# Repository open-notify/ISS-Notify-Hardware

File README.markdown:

# ISS Notify Hardware

ISS Notify is an open hardware project to make a desktop notification lamp
specifically for overhead passes for the International Space Station for a
users location.

ISS Notify is a simple 2 layer board with an AVR microcontroller with USB
and a set of RGB LEDs LED driver/shift registers. It also has a 
real time clock and a LiPo batter charging circuit.

This repo has all of the design files needed for producing the hardware.

Designed in Eagle version 6.3.

Licensed under the TAPR Open Hardware License (www.tapr.org/OHL). See 
LICENSE.txt for full license information.

 - Download pdf [schematic.pdf](https://github.com/open-notify/ISS-Notify-Hardware/raw/master/schematic.pdf)

 - Download pdf [board.pdf](https://github.com/open-notify/ISS-Notify-Hardware/raw/master/board.pdf)

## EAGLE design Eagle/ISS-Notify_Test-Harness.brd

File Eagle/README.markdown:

# Eagle Files

 - `eagle.epf`: Eagle project
 - `ISS-Notify.lbr`: Eagle parts library
 - `ISS-Notify.sch`: Main board schematic
 - `ISS-Notify.brd`: Main board boardfile
 - `ISS-Notify_Test-Harness.sch`: Test Harness schematic
 - `ISS-Notify_Test-Harness.brd`: Test Harness board

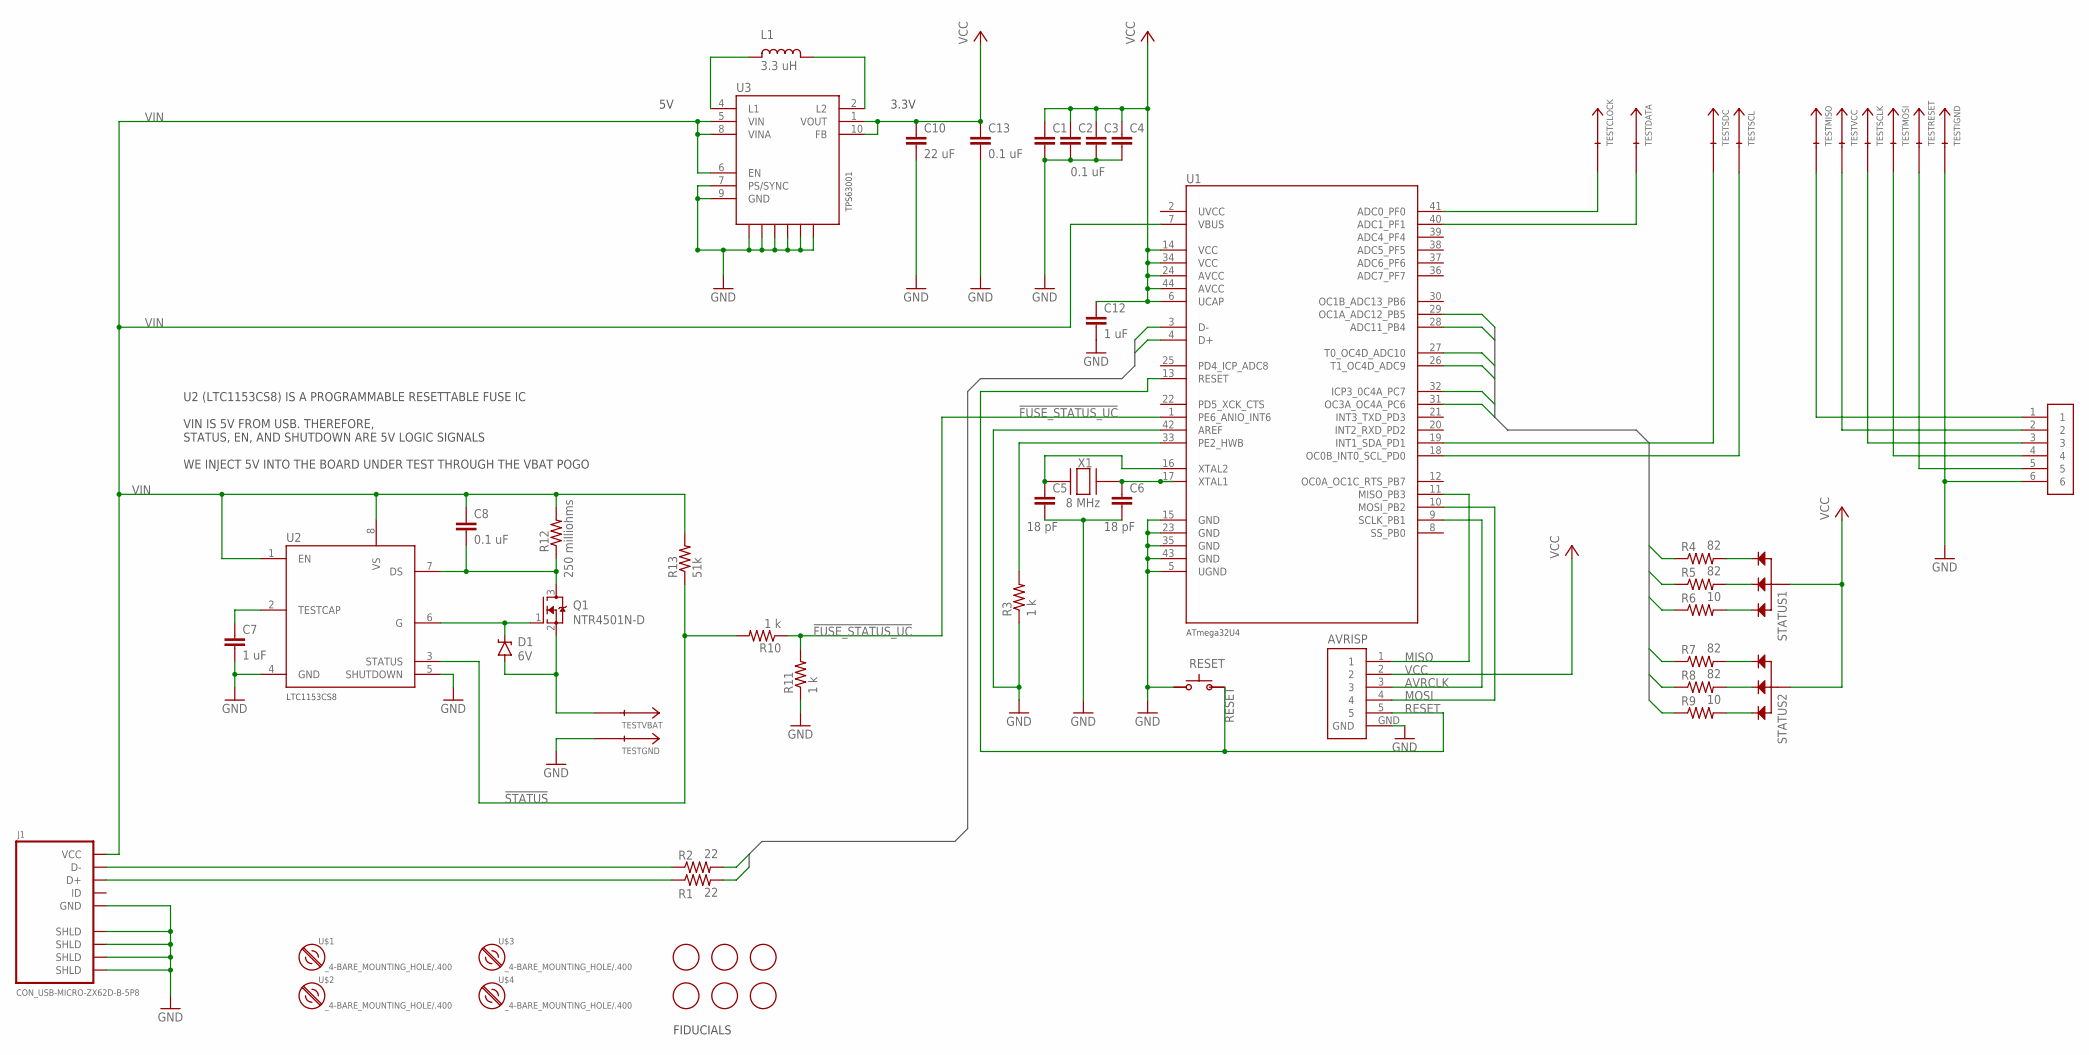
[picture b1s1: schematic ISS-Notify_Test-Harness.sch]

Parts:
AVRISP: AVRISP
C1, C2, C3, C4, C8, C13: 0.1 uF; 0603-C-NOSILK
C5, C6: 18 pF; 0603-C-NOSILK
C7, C12: 1 uF; 0603-C-NOSILK
C10: 22 uF; 0805-C-NOSILK
D1: 6V; SOD-323
F1, F2, F3, F4, F5, F6: FIDUCIAL; FIDUCIAL_1MM
J1: CON_USB-MICRO-ZX62D-B-5P8; USBMICROSMT-HIROSE
JPROGRAMER: 6HEADER; 6HEAD
L1: 3.3 uH; 0805-C-NOSILK
Q1: NTR4501N-D; SOT-23
R1, R2: 22; 0603-C-NOSILK
R3, R10, R11: 1 k; 0603-C-NOSILK
R4, R5, R7, R8: 82; 0603-C-NOSILK
R6, R9: 10; 0603-C-NOSILK
R12: 250 milliohms; 0603-C-NOSILK
R13: 51k; 0603-C-NOSILK
RESET: SWITCH
STATUS1, STATUS2: RGBLED; SMDRGBLED
TESTCLOCK: POGOPIN
TESTDATA: POGOPIN
TESTGND: POGOPIN
TESTIGND: POGOPIN
TESTMISO: POGOPIN
TESTMOSI: POGOPIN
TESTRESET: POGOPIN
TESTSCL: POGOPIN
TESTSCLK: POGOPIN
TESTSDC: POGOPIN
TESTVBAT: POGOPIN
TESTVCC: POGOPIN
U1: ATMEGA32U4; TQFP-44
U2: LTC1153CS8; SO-8
U3: TPS63001; QFN10
U$1, U$2, U$3, U$4: _4-BARE_MOUNTING_HOLE/.400; _4/.400-BARE+STD_TOOL_CLEARANCE
X1: 8 MHz; CX5Z

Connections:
!FUSE_STATUS_UC: R10.1, R11.2, U1.1 (PE6_ANIO_INT6)
!STATUS: R10.2, R13.1, U2.3 (STATUS)
AVRCLK: AVRISP.3, U1.9 (SCLK_PB1)
D+: R1.2, U1.4 (D+)
D-: R2.2, U1.3 (D-)
GND: AVRISP.GND, C1.2, C2.2, C3.2, C4.2, C5.2, C6.2, C7.2, C10.2, C12.2, C13.2, J1.P5 (GND), J1.P$1 (SHLD), J1.P$2 (SHLD), J1.P$3 (SHLD), J1.P$4 (SHLD), JPROGRAMER.6, R3.1, R11.1, RESET.3 (2), TESTGND.1, TESTIGND.1, U1.5 (UGND), U1.15 (GND), U1.23 (GND), U1.35 (GND), U1.42 (AREF), U1.43 (GND), U2.4 (GND), U2.5 (SHUTDOWN), U3.3 (PGND), U3.7 (PS/SYNC), U3.9 (GND), U3.PAD (GNDPAD), U3.PGND1, U3.PGND2, U3.PGND3, U3.PGND4
LED1_B: R6.1, U1.29 (OC1A_ADC12_PB5)
LED1_G: R5.1, U1.32 (ICP3_0C4A_PC7)
LED1_R: R4.1, U1.31 (OC3A_OC4A_PC6)
LED2_B: R9.1, U1.26 (T1_OC4D_ADC9)
LED2_G: R8.1, U1.28 (ADC11_PB4)
LED2_R: R7.1, U1.27 (T0_OC4D_ADC10)
LED_CLK: TESTCLOCK.1, U1.41 (ADC0_PF0)
LED_DATA: TESTDATA.1, U1.40 (ADC1_PF1)
MISO: AVRISP.1, U1.11 (MISO_PB3)
MOSI: AVRISP.4, U1.10 (MOSI_PB2)
unnamed: L1.1 (A), U3.4 (L1)
unnamed: L1.2 (C), U3.2 (L2)
unnamed: R4.2, STATUS1.RED (R)
unnamed: J1.P3 (D+), R1.1
unnamed: J1.P2 (D-), R2.1
unnamed: C5.1, U1.16 (XTAL2), X1.1
unnamed: R5.2, STATUS1.GREEN (G)
unnamed: R6.2, STATUS1.BLUE (B)
unnamed: R7.2, STATUS2.RED (R)
unnamed: C6.1, U1.17 (XTAL1), X1.3 (2)
unnamed: R8.2, STATUS2.GREEN (G)
unnamed: R9.2, STATUS2.BLUE (B)
unnamed: C7.1, U2.2 (TESTCAP)
unnamed: C8.2, Q1.3 (D), R12.1, U2.7 (DS)
unnamed: D1.C, Q1.1 (G), U2.6 (G)
unnamed: D1.A, Q1.2 (S), TESTVBAT.1
unnamed: R3.2, U1.33 (PE2_HWB)
RESET: AVRISP.5, RESET.1, U1.13 (RESET)
SCL: TESTSCL.1, U1.18 (OC0B_INT0_SCL_PD0)
SDA: TESTSDC.1, U1.19 (INT1_SDA_PD1)
TESTMISO: JPROGRAMER.1, TESTMISO.1
TESTMOSI: JPROGRAMER.4, TESTMOSI.1
TESTRESET: JPROGRAMER.5, TESTRESET.1
TESTSCLK: JPROGRAMER.3, TESTSCLK.1
TESTVCC: JPROGRAMER.2, TESTVCC.1
UVCC: U1.2 (UVCC)
VCC: AVRISP.2, C1.1, C2.1, C3.1, C4.1, C10.1, C12.1, C13.1, STATUS1.ANODE, STATUS2.ANODE, U1.6 (UCAP), U1.14 (VCC), U1.24 (AVCC), U1.34 (VCC), U1.44 (AVCC), U3.1 (VOUT), U3.10 (FB)
VIN: C8.1, J1.P1 (VCC), R12.2, R13.2, U1.7 (VBUS), U2.1 (EN), U2.8 (VS), U3.5 (VIN), U3.6 (EN), U3.8 (VINA)

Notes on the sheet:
3.3V
U2 (LTC1153CS8) IS A PROGRAMMABLE RESETTABLE FUSE IC VIN IS 5V FROM USB. THEREFORE, STATUS, EN, AND SHUTDOWN ARE 5V LOGIC SIGNALS WE INJECT 5V INTO THE BOARD UNDER TEST THROUGH THE VBAT POGO
FIDUCIALS

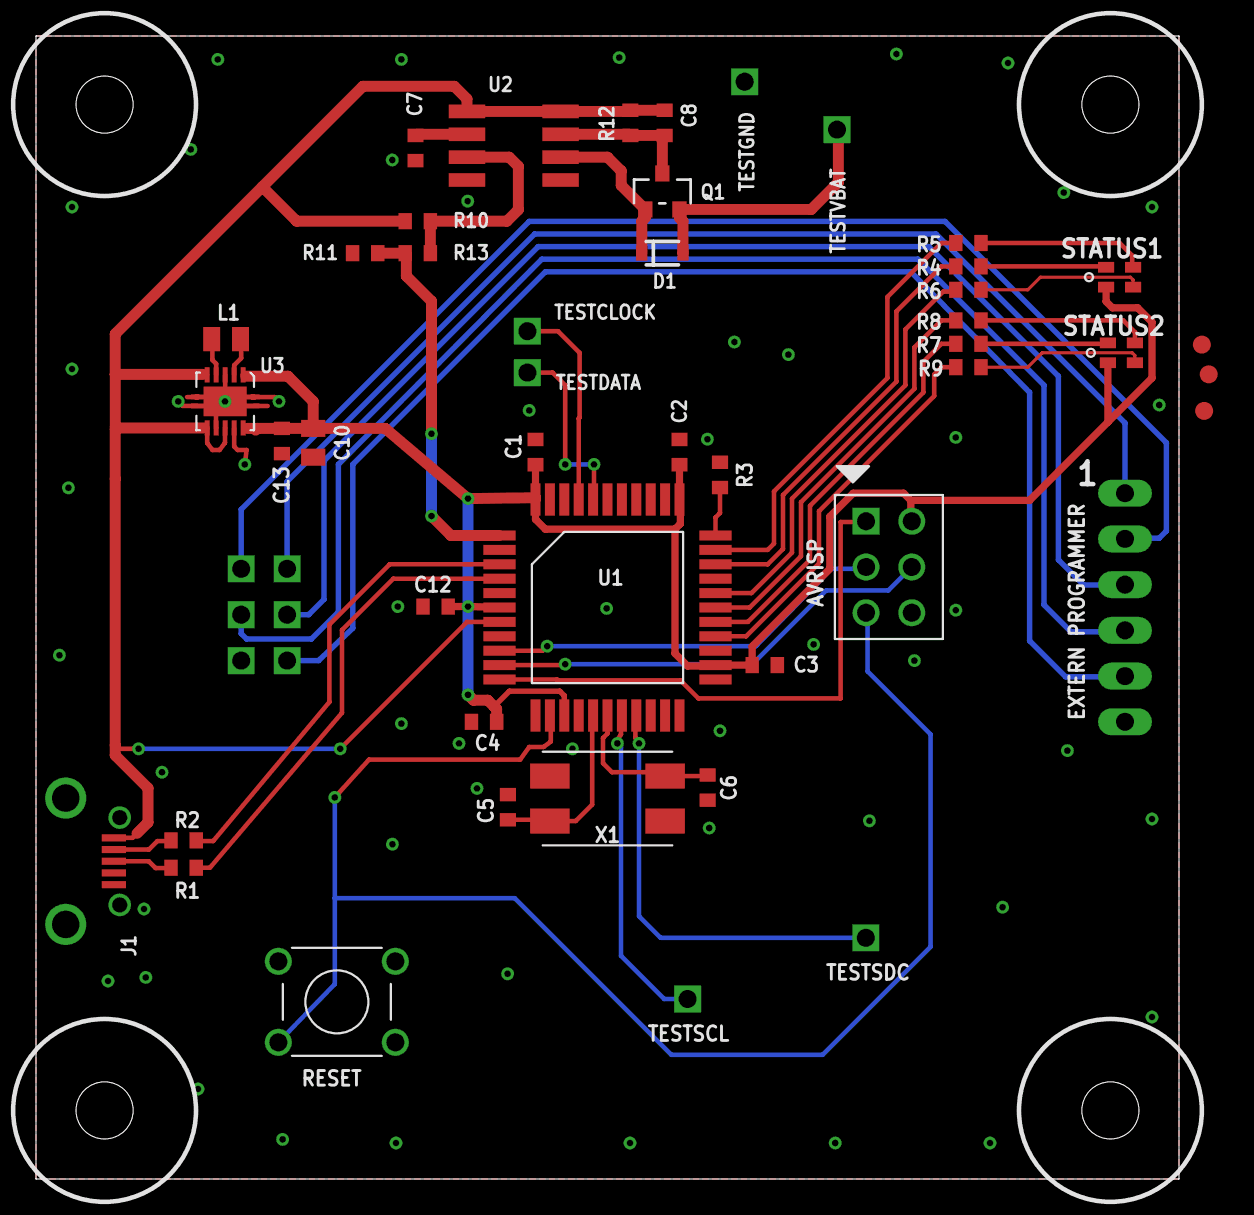
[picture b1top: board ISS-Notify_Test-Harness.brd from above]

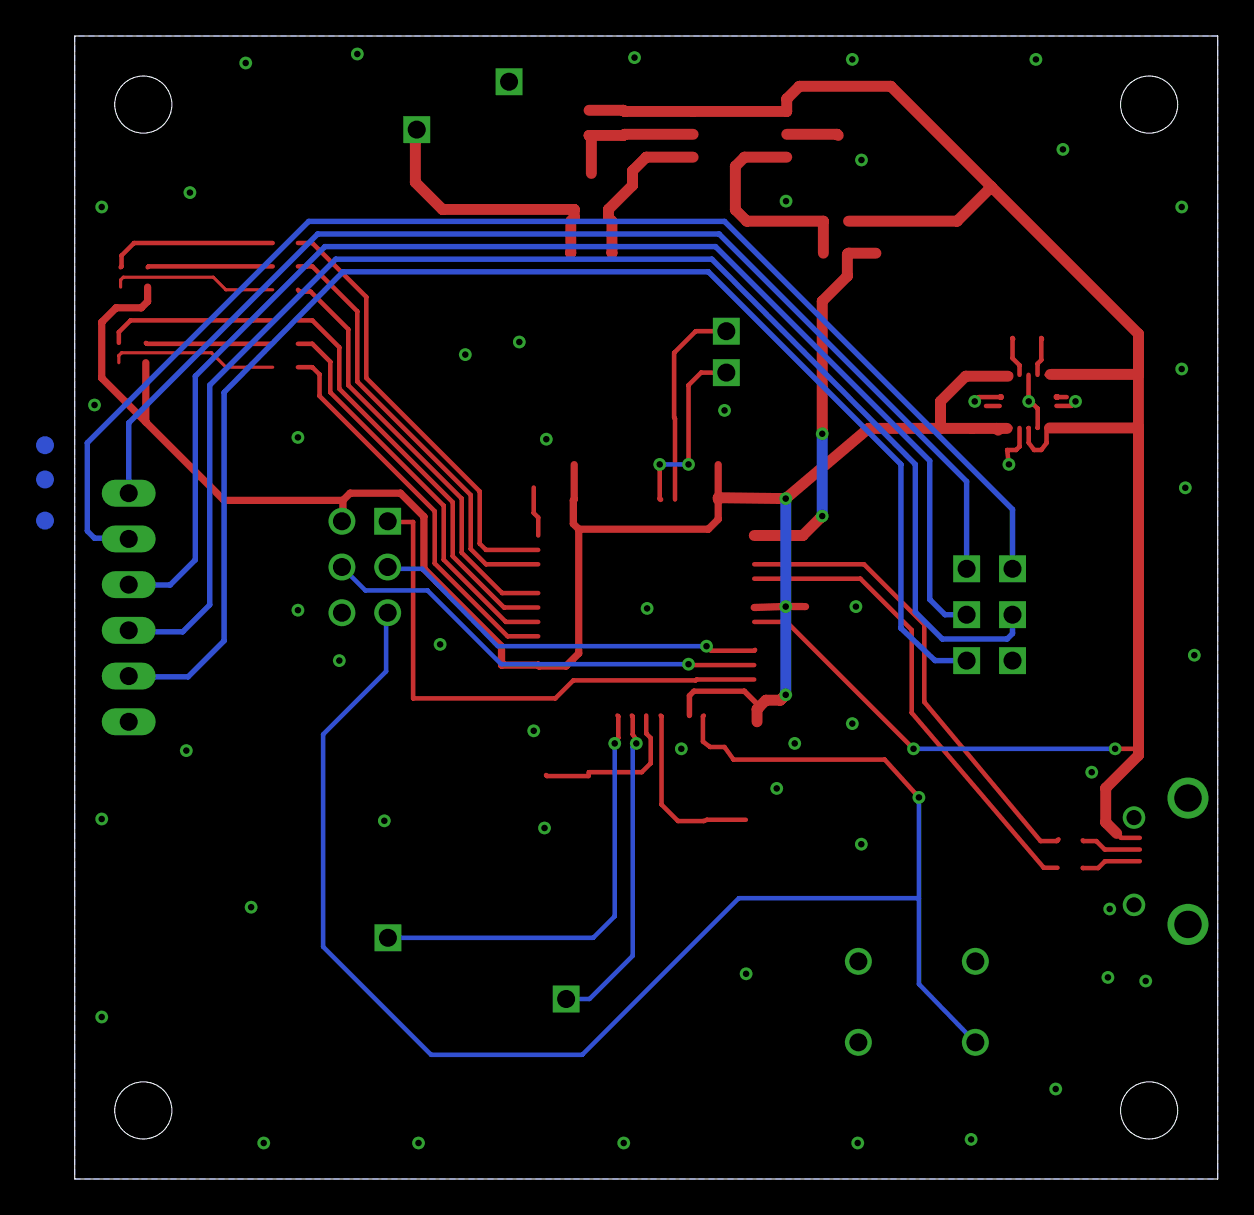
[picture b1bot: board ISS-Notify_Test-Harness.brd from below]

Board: 2 copper layers, 63.5 x 63.5 mm, 59 parts (3 on the bottom side), 43 nets.

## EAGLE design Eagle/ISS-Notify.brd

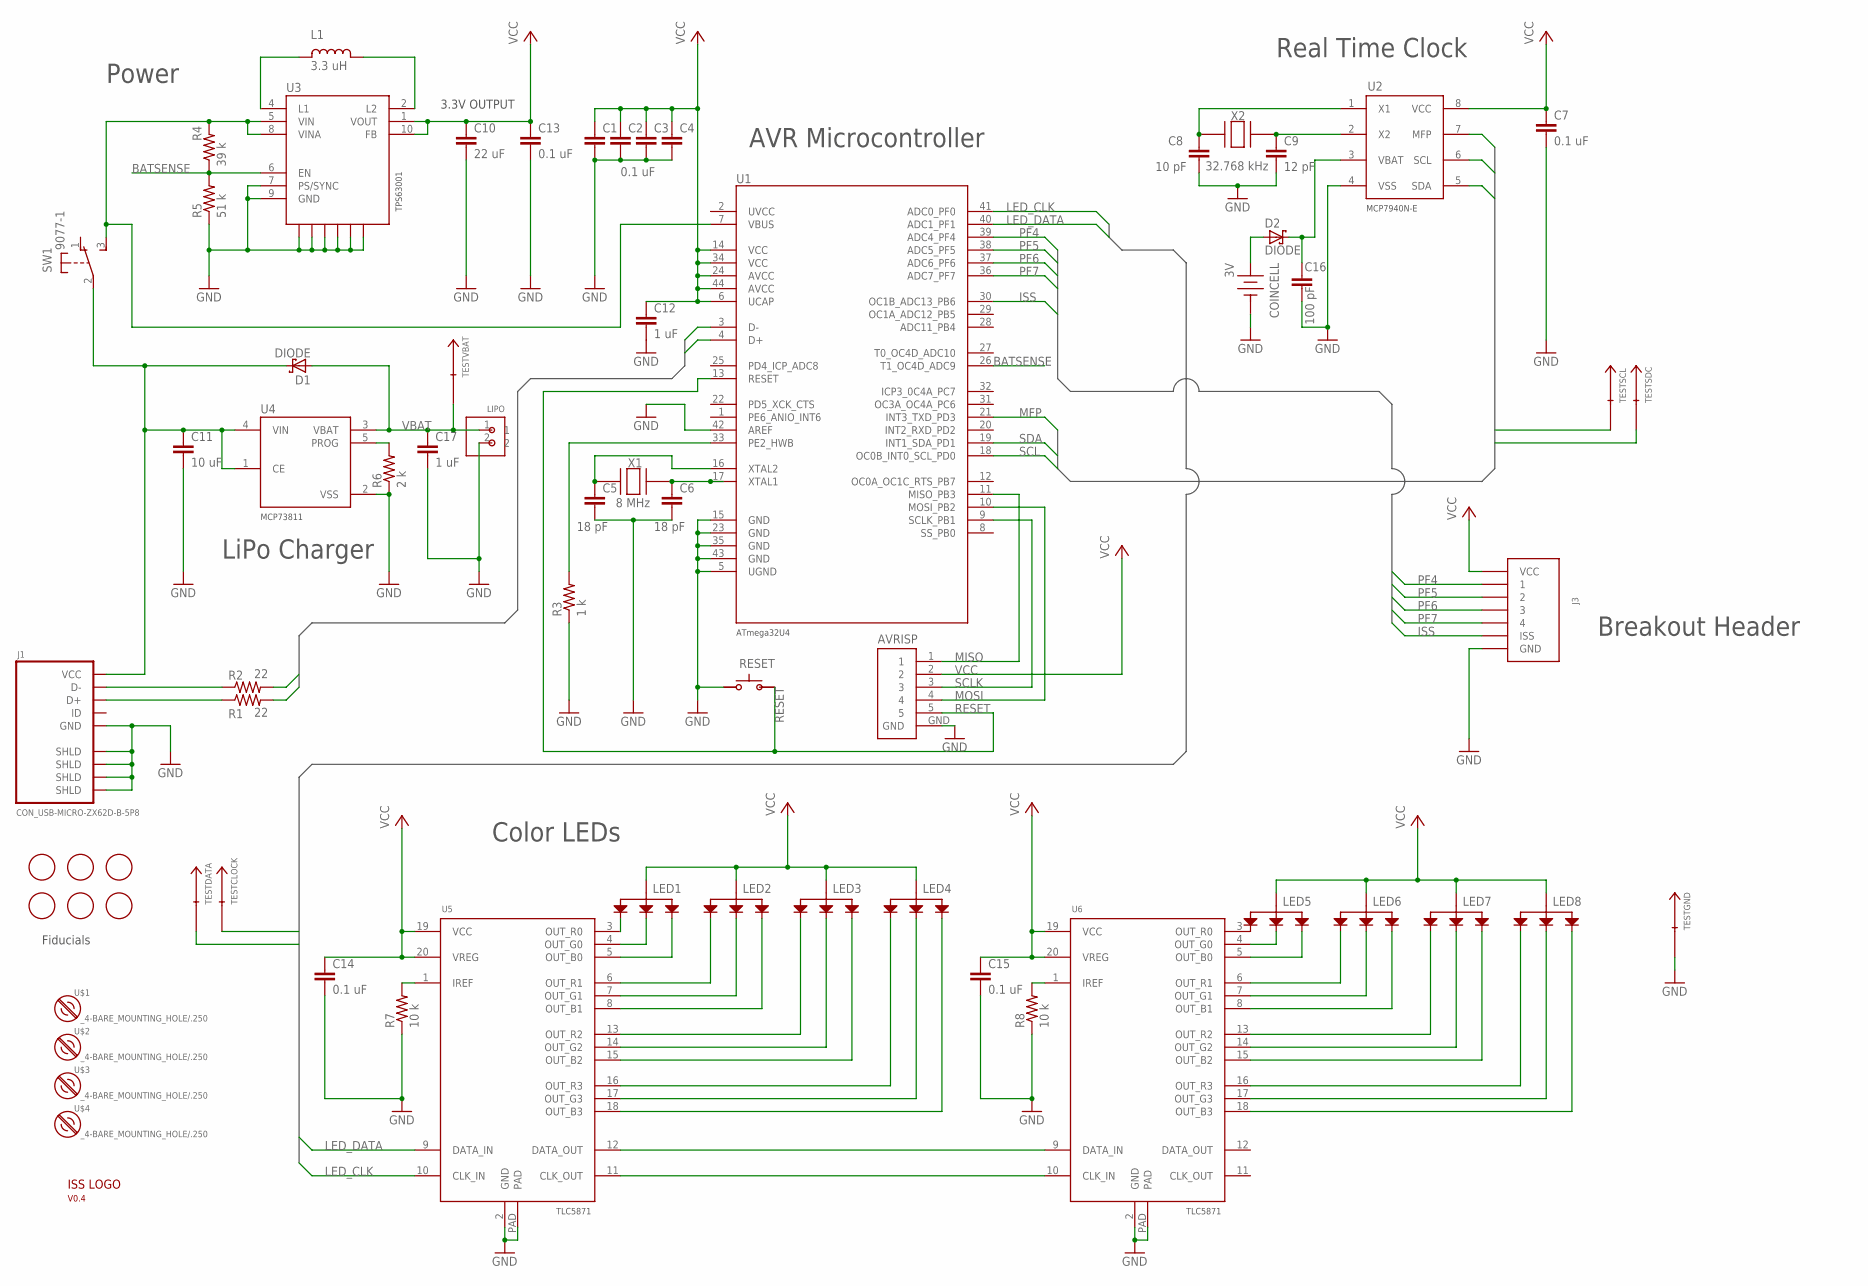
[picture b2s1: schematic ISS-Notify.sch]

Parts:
AVRISP: AVRISP
C1, C2, C3, C4, C7, C13, C14, C15: 0.1 uF; 0603-C-NOSILK
C5, C6: 18 pF; 0603-C-NOSILK
C8: 10 pF; 0603-C-NOSILK
C9: 12 pF; 0603-C-NOSILK
C10: 22 uF; 0805-C-NOSILK
C11: 10 uF; 0805-C-NOSILK
C12, C17: 1 uF; 0603-C-NOSILK
C16: 100 pF; 0603-C-NOSILK
COINCELL: 3V; COINCELL
D1, D2: DIODE; 0805-DIODE
J1: CON_USB-MICRO-ZX62D-B-5P8; USBMICROSMT-HIROSE
J3: PROTOSPACE2
L1: 3.3 uH; 0805-C-NOSILK
LED1, LED2, LED3, LED4, LED5, LED6, LED7, LED8: RGBLED; SMDRGBLED
LIPO: JST2; JSTHEAD
R1, R2: 22; 0603-C-NOSILK
R3: 1 k; 0603-C-NOSILK
R4: 39 k; 0603-C-NOSILK
R5: 51 k; 0603-C-NOSILK
R6: 2 k; 0603-C-NOSILK
R7, R8: 10 k; 0603-C-NOSILK
RESET: SWITCH
SW1: 9077-1; ESWITCH
TESTCLOCK: TESTPIN
TESTDATA: TESTPIN
TESTGND: TESTPIN
TESTSCL: TESTPIN
TESTSDC: TESTPIN
TESTVBAT: TESTPIN
U1: ATMEGA32U4; TQFP-44
U2: MCP7940N
U3: TPS63001; QFN10
U4: MCP73811; SOT23-5L
U5, U6: TLC5971; R-PDSO-G20
U$1, U$2, U$3, U$4: _4-BARE_MOUNTING_HOLE/.250; _4/.250-BARE+STD_WASHER
U$5: V0.4; LOGO
U$6, U$7, U$8, U$9, U$10, U$11: FIDUCIAL; FIDUCIAL_1MM
X1: 8 MHz; CX5Z
X2: 32.768 kHz; ABS10

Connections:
BATSENSE: R4.1, R5.2, U1.26 (T1_OC4D_ADC9), U3.6 (EN)
D+: R1.2, U1.4 (D+)
D-: R2.2, U1.3 (D-)
GND: AVRISP.GND, C1.2, C2.2, C3.2, C4.2, C5.2, C6.2, C7.2, C8.2, C9.2, C10.2, C11.2, C12.2, C13.2, C14.2, C15.2, C16.2, C17.2, COINCELL.GND, J1.P5 (GND), J1.P$1 (SHLD), J1.P$2 (SHLD), J1.P$3 (SHLD), J1.P$4 (SHLD), J3.GND, LIPO.2, R3.1, R5.1, R6.1, R7.1, R8.1, RESET.3 (2), TESTGND.P$1, U1.5 (UGND), U1.15 (GND), U1.23 (GND), U1.35 (GND), U1.42 (AREF), U1.43 (GND), U2.4 (VSS), U3.3 (PGND), U3.7 (PS/SYNC), U3.9 (GND), U3.PAD (GNDPAD), U3.PGND1, U3.PGND2, U3.PGND3, U3.PGND4, U4.2 (VSS), U5.2 (GND), U5.PAD, U6.2 (GND), U6.PAD
ISS: J3.ISS, U1.30 (OC1B_ADC13_PB6)
LED_CLK: TESTCLOCK.P$1, U1.41 (ADC0_PF0), U5.10 (CLK_IN)
LED_DATA: TESTDATA.P$1, U1.40 (ADC1_PF1), U5.9 (DATA_IN)
MFP: U1.21 (INT3_TXD_PD3), U2.7 (MFP)
MISO: AVRISP.1, U1.11 (MISO_PB3)
MOSI: AVRISP.4, U1.10 (MOSI_PB2)
unnamed: L1.1 (A), U3.4 (L1)
unnamed: L1.2 (C), U3.2 (L2)
unnamed: J1.P3 (D+), R1.1
unnamed: J1.P2 (D-), R2.1
unnamed: C5.1, U1.16 (XTAL2), X1.1
unnamed: C9.1, U2.2 (X2), X2.@1 (2)
unnamed: C8.1, U2.1 (X1), X2.1
unnamed: C6.1, U1.17 (XTAL1), X1.3 (2)
unnamed: COINCELL.POS1 (VBAT), D2.A
unnamed: R6.2, U4.5 (PROG)
unnamed: U5.11 (CLK_OUT), U6.10 (CLK_IN)
unnamed: U5.12 (DATA_OUT), U6.9 (DATA_IN)
unnamed: C16.1, D2.C, U2.3 (VBAT)
unnamed: LED2.BLUE (B), U5.8 (OUT_B1)
unnamed: R7.2, U5.1 (IREF)
unnamed: R8.2, U6.1 (IREF)
unnamed: LED3.RED (R), U5.13 (OUT_R2)
unnamed: LED3.GREEN (G), U5.14 (OUT_G2)
unnamed: LED3.BLUE (B), U5.15 (OUT_B2)
unnamed: LED1.RED (R), U5.3 (OUT_R0)
unnamed: LED1.GREEN (G), U5.4 (OUT_G0)
unnamed: LED1.BLUE (B), U5.5 (OUT_B0)
unnamed: LED2.RED (R), U5.6 (OUT_R1)
unnamed: LED2.GREEN (G), U5.7 (OUT_G1)
unnamed: LED4.RED (R), U5.16 (OUT_R3)
unnamed: LED4.GREEN (G), U5.17 (OUT_G3)
unnamed: LED4.BLUE (B), U5.18 (OUT_B3)
unnamed: LED7.RED (R), U6.13 (OUT_R2)
unnamed: LED5.RED (R), U6.3 (OUT_R0)
unnamed: LED5.GREEN (G), U6.4 (OUT_G0)
unnamed: LED5.BLUE (B), U6.5 (OUT_B0)
unnamed: LED6.RED (R), U6.6 (OUT_R1)
unnamed: LED6.GREEN (G), U6.7 (OUT_G1)
unnamed: LED6.BLUE (B), U6.8 (OUT_B1)
unnamed: LED7.GREEN (G), U6.14 (OUT_G2)
unnamed: LED7.BLUE (B), U6.15 (OUT_B2)
unnamed: LED8.RED (R), U6.16 (OUT_R3)
unnamed: LED8.GREEN (G), U6.17 (OUT_G3)
unnamed: LED8.BLUE (B), U6.18 (OUT_B3)
unnamed: R3.2, U1.33 (PE2_HWB)
PF4: J3.1, U1.39 (ADC4_PF4)
PF5: J3.2, U1.38 (ADC5_PF5)
PF6: J3.3, U1.37 (ADC6_PF6)
PF7: J3.4, U1.36 (ADC7_PF7)
RESET: AVRISP.5, RESET.1, U1.13 (RESET)
SCL: TESTSCL.P$1, U1.18 (OC0B_INT0_SCL_PD0), U2.6 (SCL)
SCLK: AVRISP.3, U1.9 (SCLK_PB1)
SDA: TESTSDC.P$1, U1.19 (INT1_SDA_PD1), U2.5 (SDA)
UVCC: U1.2 (UVCC)
VBAT: C17.1, D1.A, LIPO.1, TESTVBAT.P$1, U4.3 (VBAT)
VCC: AVRISP.2, C1.1, C2.1, C3.1, C4.1, C7.1, C10.1, C12.1, C13.1, C14.1, C15.1, J3.VCC, LED1.ANODE, LED2.ANODE, LED3.ANODE, LED4.ANODE, LED5.ANODE, LED6.ANODE, LED7.ANODE, LED8.ANODE, U1.6 (UCAP), U1.14 (VCC), U1.24 (AVCC), U1.34 (VCC), U1.44 (AVCC), U2.8 (VCC), U3.1 (VOUT), U3.10 (FB), U5.19 (VCC), U5.20 (VREG), U6.19 (VCC), U6.20 (VREG)
VIN: R4.2, SW1.3 (S), U1.7 (VBUS), U3.5 (VIN), U3.8 (VINA)
VUSB: C11.1, D1.C, J1.P1 (VCC), SW1.2, U4.1 (CE), U4.4 (VIN)

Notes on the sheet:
LiPo Charger
Power
AVR Microcontroller
Real Time Clock
Color LEDs
Breakout Header
Fiducials
3.3V OUTPUT

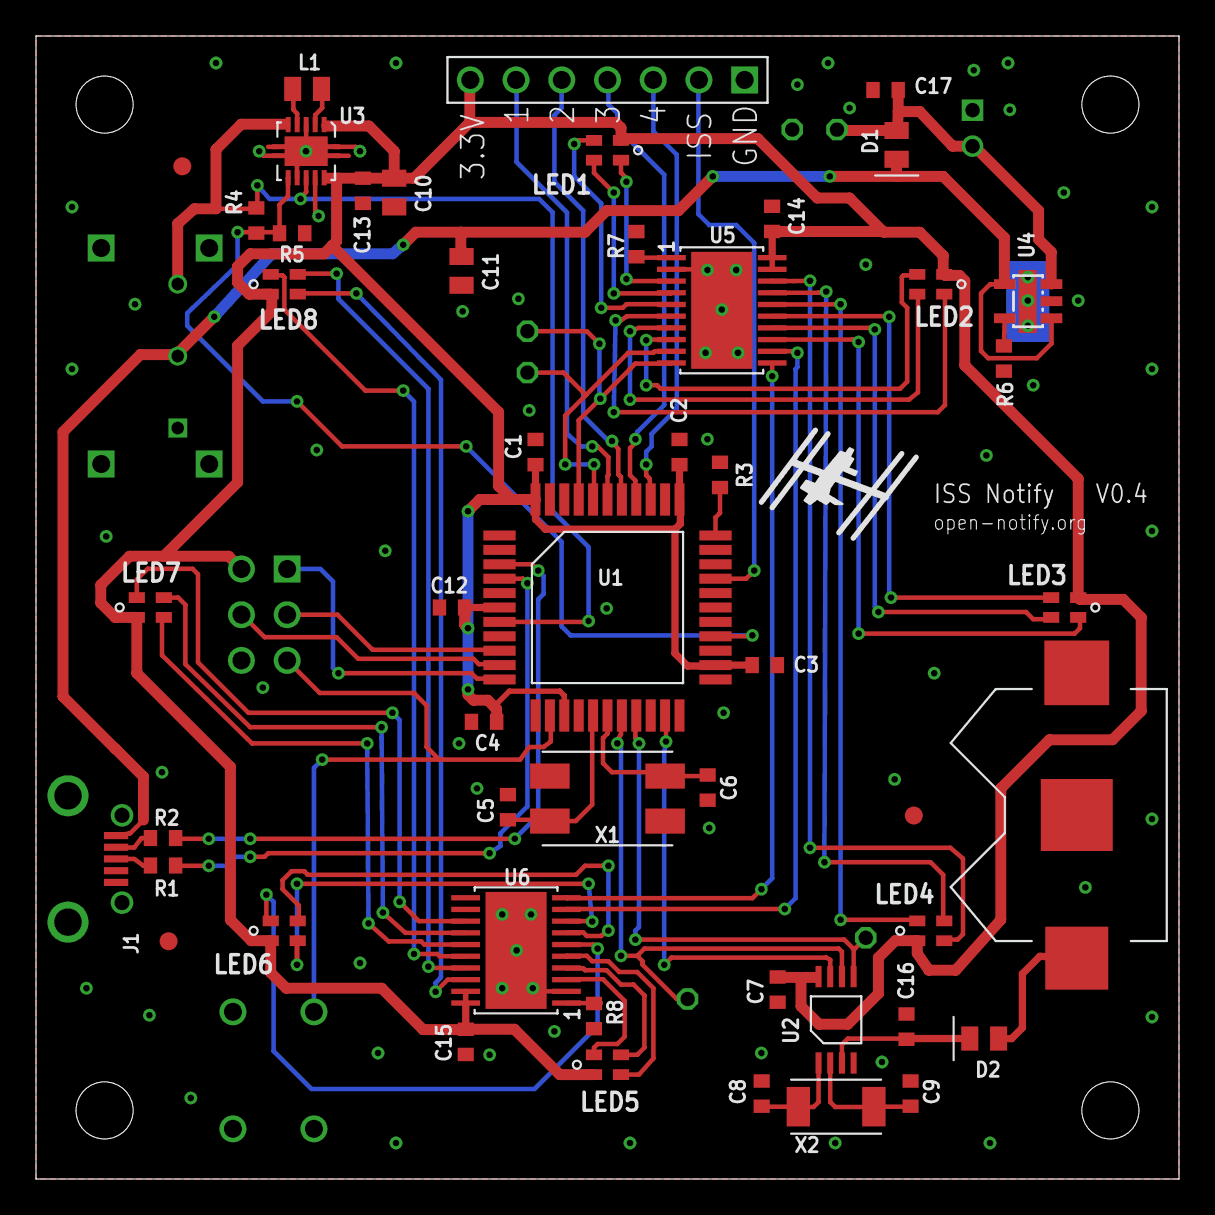
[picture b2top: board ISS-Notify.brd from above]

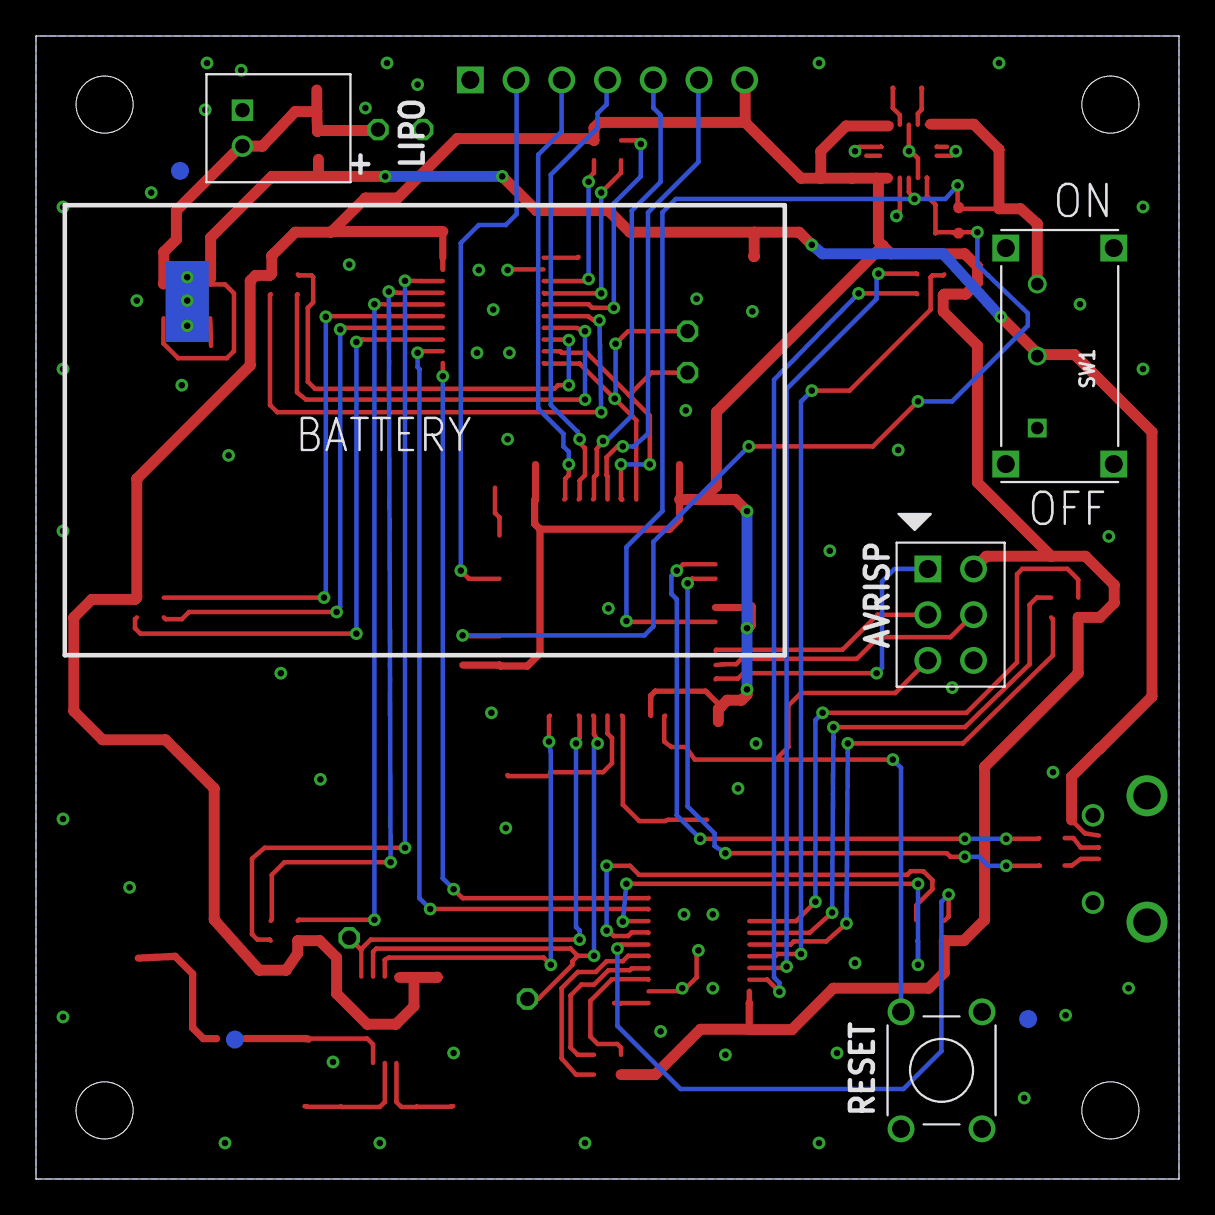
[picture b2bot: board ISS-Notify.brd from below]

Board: 2 copper layers, 63.5 x 63.5 mm, 68 parts (7 on the bottom side), 62 nets.

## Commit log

2011-08-11 first commit, work so far
2011-10-17 Added LED circle and LED driver
2011-10-27 moved things around for clarity
2011-10-27 Added AVR_ISP
2011-12-08 corrections and connections and decoupling capaciters
2011-12-08 protoboard space
2011-12-09 8 MHz crystal for ATMEGA
2011-12-30 tweaks
2011-12-31 rework with buses and added LiPo support
2011-12-31 Eagle folder and datasheets
2011-12-31 busses everywhere
2011-12-31 Added battery charger into uc
2011-12-31 preview image
2011-12-31 testing image in readme
2012-01-01 smaller frame
2012-01-02 added p-channel mosfet
2012-01-02 voltage dividers
2012-01-04 Mostly large cosmetic changes to the schematic and careful looking for bugs. Removed SOUT short to ground, removed unecessary diode in Vbus path, added issue list, fixed battery measurement circuit, 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
2012-01-04 Ran ERC and fixed important warnings and approved stupid ones. Fixes: invoked uninvoked pins on USB connector, STAT1 was connected to uC twice, GBLANK was misnamed in nets.
2012-01-07 removed UVCC
2012-01-07 Part names, fixed some parts, some double checking
2012-01-08 more parts double checked, fixed RTC package
2012-01-08 replaced TPS3205 with TPS63001
2012-01-08 finished picking through the RTC, added pretty BOM
2012-01-10 furthur nit picking. All but a couple of parts fixed, everything listed in BOM
2012-01-10 added protospace and pdf of schematic
2012-01-12 added SMT USB micro B connector
2012-01-16 bom colours
2012-01-16 switch and better C2 cap
2012-01-17 fixes
2012-01-17 first board design ratsnest
2012-01-17 routing R and G LEDs
2012-01-18 LED hookups and RTC layout
2012-01-18 gitignore file
2012-01-18 updated schematic image and pdf. moved LED drives slightly to the right
2012-01-20 wireing protospace
2012-01-26 groung planes
2012-02-13 tweaked ground plane
2012-03-07 Started laying power
2012-03-23 improved pwr routing
2012-03-24 Layout ver 1
2012-04-01 power pad
2012-04-02 Faceplate lasercut svg
2012-04-06 Fixes, fixes, and DRC checkout
2012-04-06 Text and logos added to screen layer
2012-04-06 replaced charger part with MSOP package
2012-04-06 clean design
2012-04-06 gerber files
2012-04-10 Fixes from laying out parts on paper
2012-04-12 tweak leads for RTC
2012-04-12 Ripped up and re-routed wires from SMT pads to be centered and orthogonal to the side. Moved a few vias for better power routing.
2012-04-12 Moved a few more vias around for better ground plane.
2012-04-12 Did a DRC on all layers, fixed a tname over a via, redid ERC, approved a minor warning.
2012-04-12 Regen Gerbers
2012-04-12 Removed useless files (stupid EAGLE).
2012-04-12 Added Gerber files for proto board (v0.1)
2012-04-24 faceplate updates
2012-04-24 fonts to paths
2012-04-28 Faceplate work
2012-04-30 faceplate set for lasering
2012-10-09 version 0.2 fixes
2012-11-07 more 0.2 fixes
2012-11-07 resistor values
2012-11-07 preliminary v02 gerbers
2012-11-08 licence and documentation
2012-11-09 updated BOM
2012-11-28 removed button hole and text from faceplate
2012-11-29 backplate and faceplate update
2013-04-06 fixed some library parts
2013-04-06 github pages docs
2013-04-06 jekyll layout
2013-04-06 testing textile table markup
2013-04-06 testing table class in bom
2013-04-06 missed at period
2013-04-06 cell aligment in textile
2013-04-06 link testing in textile
2013-04-06 added a few parts
2013-04-06 genorated textile file with csv download
2013-04-06 update part number, checked in csv script
2013-04-16 bom direct from digikey
2013-04-16 clean up Eagle directory, upgrade to version 6, start small board
2013-04-17 power side of schematic
2013-04-21 LED and drivers in schematic
2013-04-21 LED driver datasheet, Frame and proto header on schematic
2013-04-21 removed cam folder, this gets packed to gerbers and can be generated anyway
2013-04-21 genorated csv and textile page from raw Digikey order quote
2013-04-21 BOM now handled in github pages
2013-04-21 finish schematic
2013-04-21 2.5 inch board
2013-04-21 power traces
2013-04-21 basic layout
2013-04-21 pre-ground plane
2013-04-21 Ground plane fill
2013-04-22 minor library updates, thermal pad under LiPo charger
2013-04-22 screen layer cleaned up
2013-04-22 tplace for push button
2013-04-22 edge ground place stipling
2013-04-22 drc passed
2013-04-22 bat sense signal
2013-04-22 connect X1 pads
2013-04-22 logo
2013-04-22 minor trace size fix
2013-04-23 Cut gerbers for OSH Park
2013-04-23 faceplate for smaller board
2013-04-23 clean up datasheet folder
2013-04-23 Update parts after digikey searches
2013-04-23 updated gerbers and documentation
2013-04-30 full BOM for small board
2013-09-17 remove wrong traces from XTAL
2013-09-17 a couple of astetic trace fixes
2013-09-17 names of J2 and reset button so they show up logicall on screenprint
2013-09-17 updated screen on proto area
2013-09-17 testpin library part
2013-09-17 test pin placement on board
2013-09-17 incrament board version on screen
2013-09-17 starting test harness board
2013-09-20 layout update
2013-09-20 ignore jekyll
2013-09-20 update bom and url routing
2013-09-20 forgot to update links in BOM table
2013-09-23 fixed annoying bolt landing, moved a via or two
2013-09-24 pogo pin landings for test harness
2013-09-24 first pass routing to pogo pins on test harness
2013-10-15 clean up power supply, 6 pin header for programming test board
2013-10-16 external programmer for test board
2013-10-16 2 rgb status LEDs
2013-10-16 route status LEDs
2013-10-16 move power supply over a little
2014-09-06 Fixed L1 packages, changed USB header. Passes ERC, DRC, rats. Ship it.
2014-09-07 Updating readme with file name correction
2014-09-09 Added fiducials per Screaming Circuits blog postw.
2014-09-13 Add fiducials to board and library. Passes DRC, ERC, rats.
2014-09-13 Add IPC-D-356 netlist. Add gerbers.
2014-09-13 Added LTC1153 package to library. Added to schematic without circuit. Needs another look in the morning.
2014-09-13 Added datasheet.
2014-09-14 Added fiducials, added note about LTC1153 fuse circuit.
2014-09-17 Harness passes ERC, DRC, rats. Ready for review. D1 part number not finalized.
2014-09-21 Changed resistor values for the LED according to datasheet
2014-10-08 Ordered this board so it'd better be right.

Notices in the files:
parts and their libraries:
SparkFun-DiscreteSemi: Licensing: Creative Commons ShareAlike 4.0 International - https://creativecommons.org/licenses/by-sa/4.0
